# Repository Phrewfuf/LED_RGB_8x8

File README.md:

LED_RGB_8x8
===========

Proof of concept for a bigger RGB LED Project

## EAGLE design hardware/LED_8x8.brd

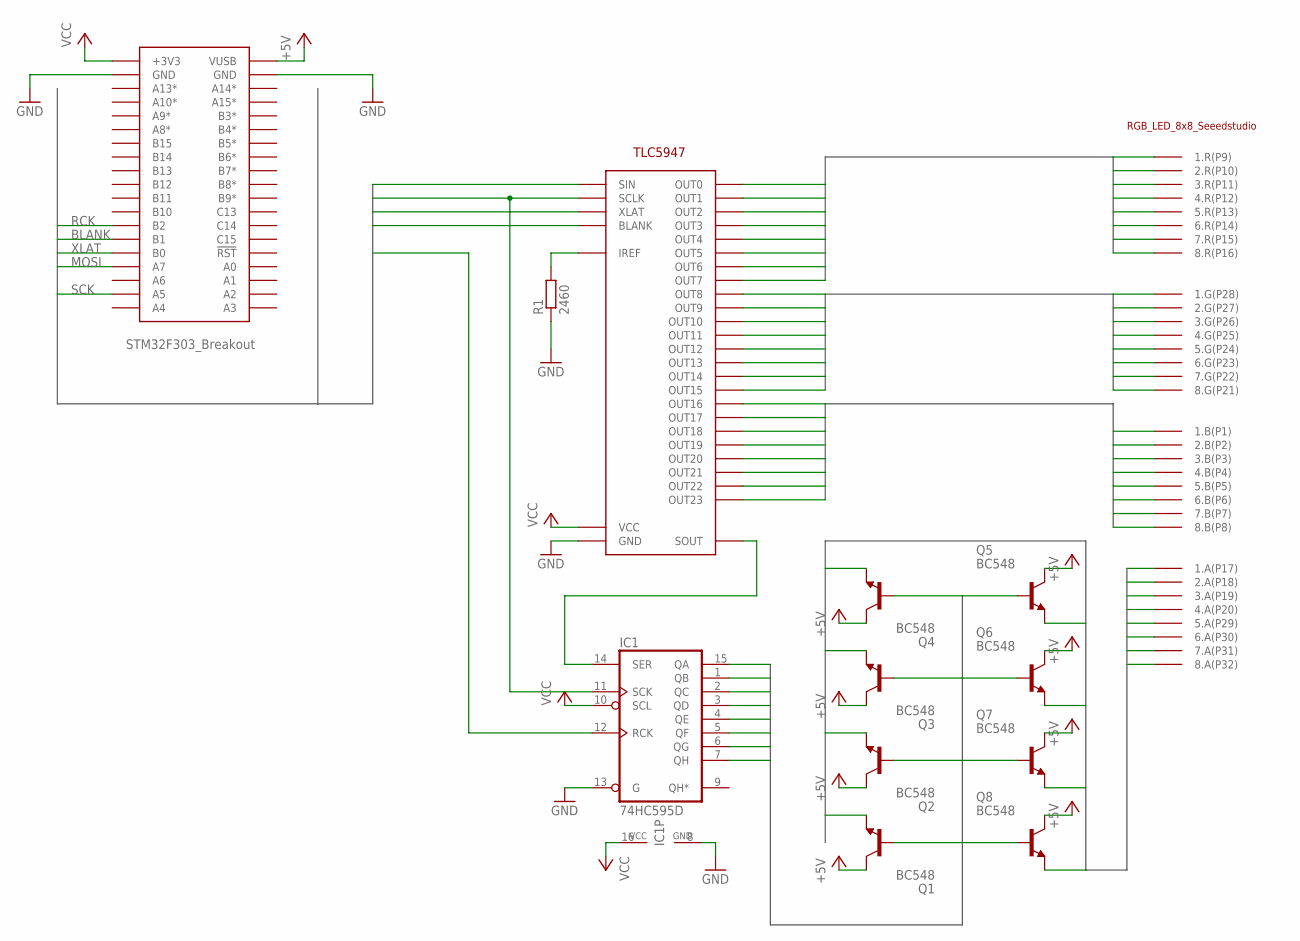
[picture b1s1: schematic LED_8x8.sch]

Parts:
IC1: 74HC595D; SO16
Q1, Q2, Q3, Q4, Q5, Q6, Q7, Q8: BC548; TO92-EBC
R1: 2460; R0603
U$1: TLC5947; TSSOP32
U$2: STM32F303_BREAKOUT; STM32_BREAKOUT
U$3: LED_RGB_8X8

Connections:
+5V: Q1.C, Q2.C, Q3.C, Q4.C, Q5.C, Q6.C, Q7.C, Q8.C, U$2.VUSB
BLANK: U$1.BLANK, U$2.B1
BLUE1: U$1.OUT16, U$3.P1 (1.B(P1))
BLUE2: U$1.OUT17, U$3.P2 (2.B(P2))
BLUE3: U$1.OUT18, U$3.P3 (3.B(P3))
BLUE4: U$1.OUT19, U$3.P4 (4.B(P4))
BLUE5: U$1.OUT20, U$3.P5 (5.B(P5))
BLUE6: U$1.OUT21, U$3.P6 (6.B(P6))
BLUE7: U$1.OUT22, U$3.P7 (7.B(P7))
BLUE8: U$1.OUT23, U$3.P8 (8.B(P8))
GND: IC1.8 (GND), IC1.13 (G), R1.1, U$1.GND, U$2.GND@1 (GND), U$2.GND@2 (GND)
GREEN1: U$1.OUT8, U$3.P28 (1.G(P28))
GREEN2: U$1.OUT9, U$3.P27 (2.G(P27))
GREEN3: U$1.OUT10, U$3.P26 (3.G(P26))
GREEN4: U$1.OUT11, U$3.P25 (4.G(P25))
GREEN5: U$1.OUT12, U$3.P24 (5.G(P24))
GREEN6: U$1.OUT13, U$3.P23 (6.G(P23))
GREEN7: U$1.OUT14, U$3.P22 (7.G(P22))
GREEN8: U$1.OUT15, U$3.P21 (8.G(P21))
MOSI: U$1.SIN, U$2.A7
unnamed: IC1.14 (SER), U$1.SOUT
unnamed: R1.2, U$1.IREF
POWERA1: Q1.E, U$3.P17 (1.A(P17))
POWERA2: Q2.E, U$3.P18 (2.A(P18))
POWERA3: Q3.E, U$3.P19 (3.A(P19))
POWERA4: Q4.E, U$3.P20 (4.A(P20))
POWERA5: Q5.E, U$3.P29 (5.A(P29))
POWERA6: Q6.E, U$3.P30 (6.A(P30))
POWERA7: Q7.E, U$3.P31 (7.A(P31))
POWERA8: Q8.E, U$3.P32 (8.A(P32))
RCK: IC1.12 (RCK), U$2.B2
RED1: U$1.OUT0, U$3.P9 (1.R(P9))
RED2: U$1.OUT1, U$3.P10 (2.R(P10))
RED3: U$1.OUT2, U$3.P11 (3.R(P11))
RED4: U$1.OUT3, U$3.P12 (4.R(P12))
RED5: U$1.OUT4, U$3.P13 (5.R(P13))
RED6: U$1.OUT5, U$3.P14 (6.R(P14))
RED7: U$1.OUT6, U$3.P15 (7.R(P15))
RED8: U$1.OUT7, U$3.P16 (8.R(P16))
SCK: IC1.11 (SCK), U$1.SCLK, U$2.A5
SHIFTA1: IC1.15 (QA), Q1.B
SHIFTA2: IC1.1 (QB), Q2.B
SHIFTA3: IC1.2 (QC), Q3.B
SHIFTA4: IC1.3 (QD), Q4.B
SHIFTA5: IC1.4 (QE), Q5.B
SHIFTA6: IC1.5 (QF), Q6.B
SHIFTA7: IC1.6 (QG), Q7.B
SHIFTA8: IC1.7 (QH), Q8.B
VCC: IC1.10 (SCL), IC1.16 (VCC), U$1.VCC, U$2.+3V3
XLAT: U$1.XLAT, U$2.B0

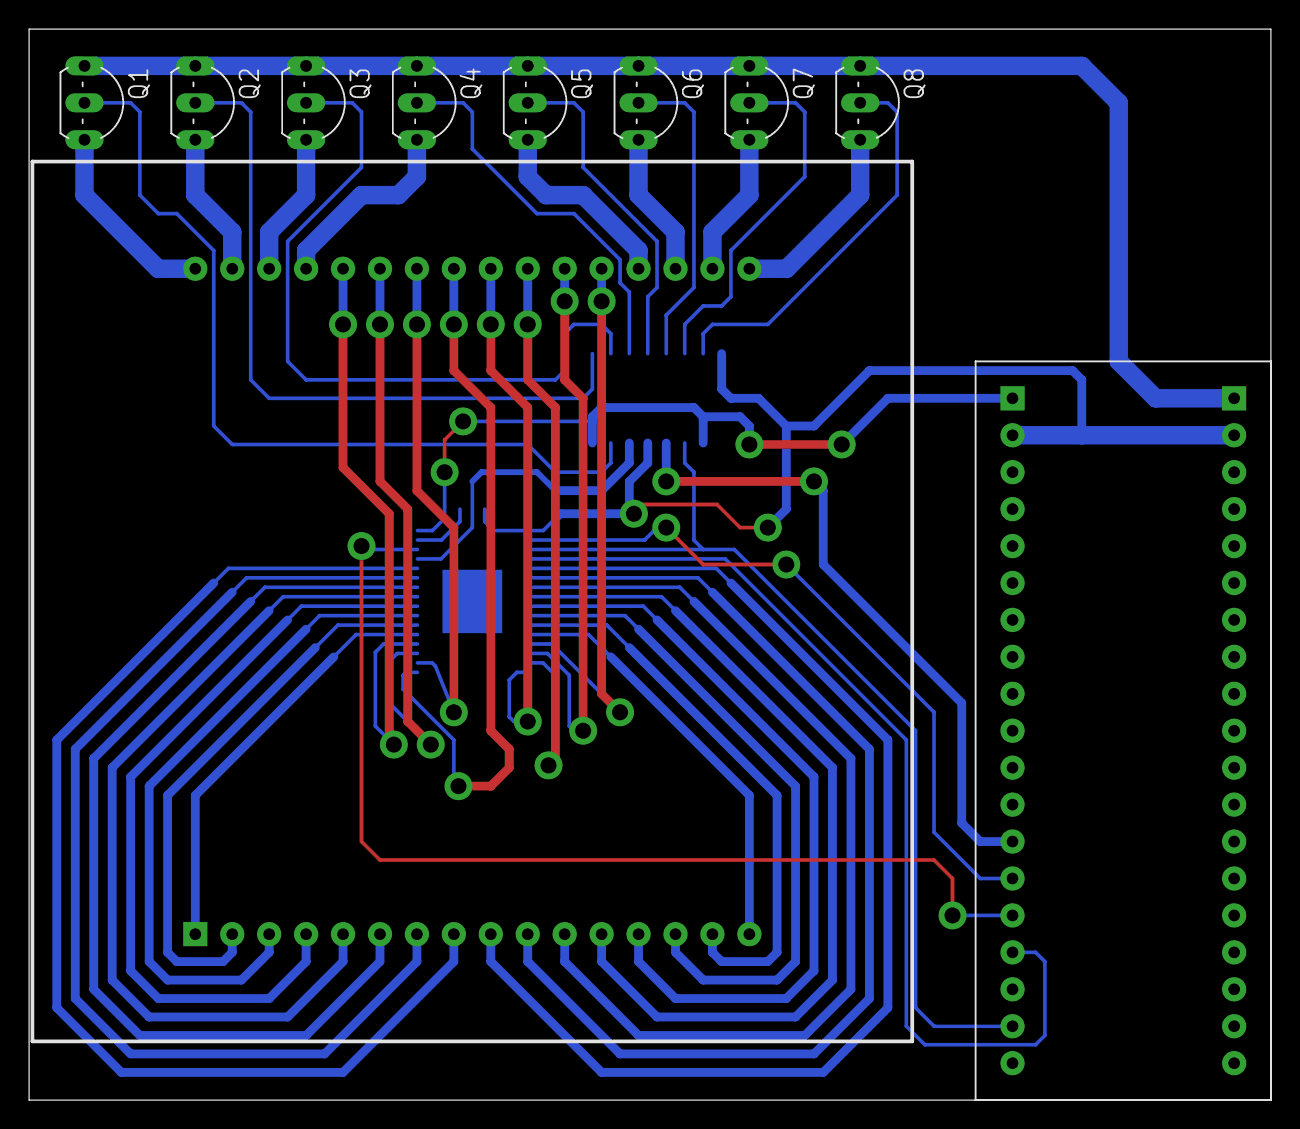
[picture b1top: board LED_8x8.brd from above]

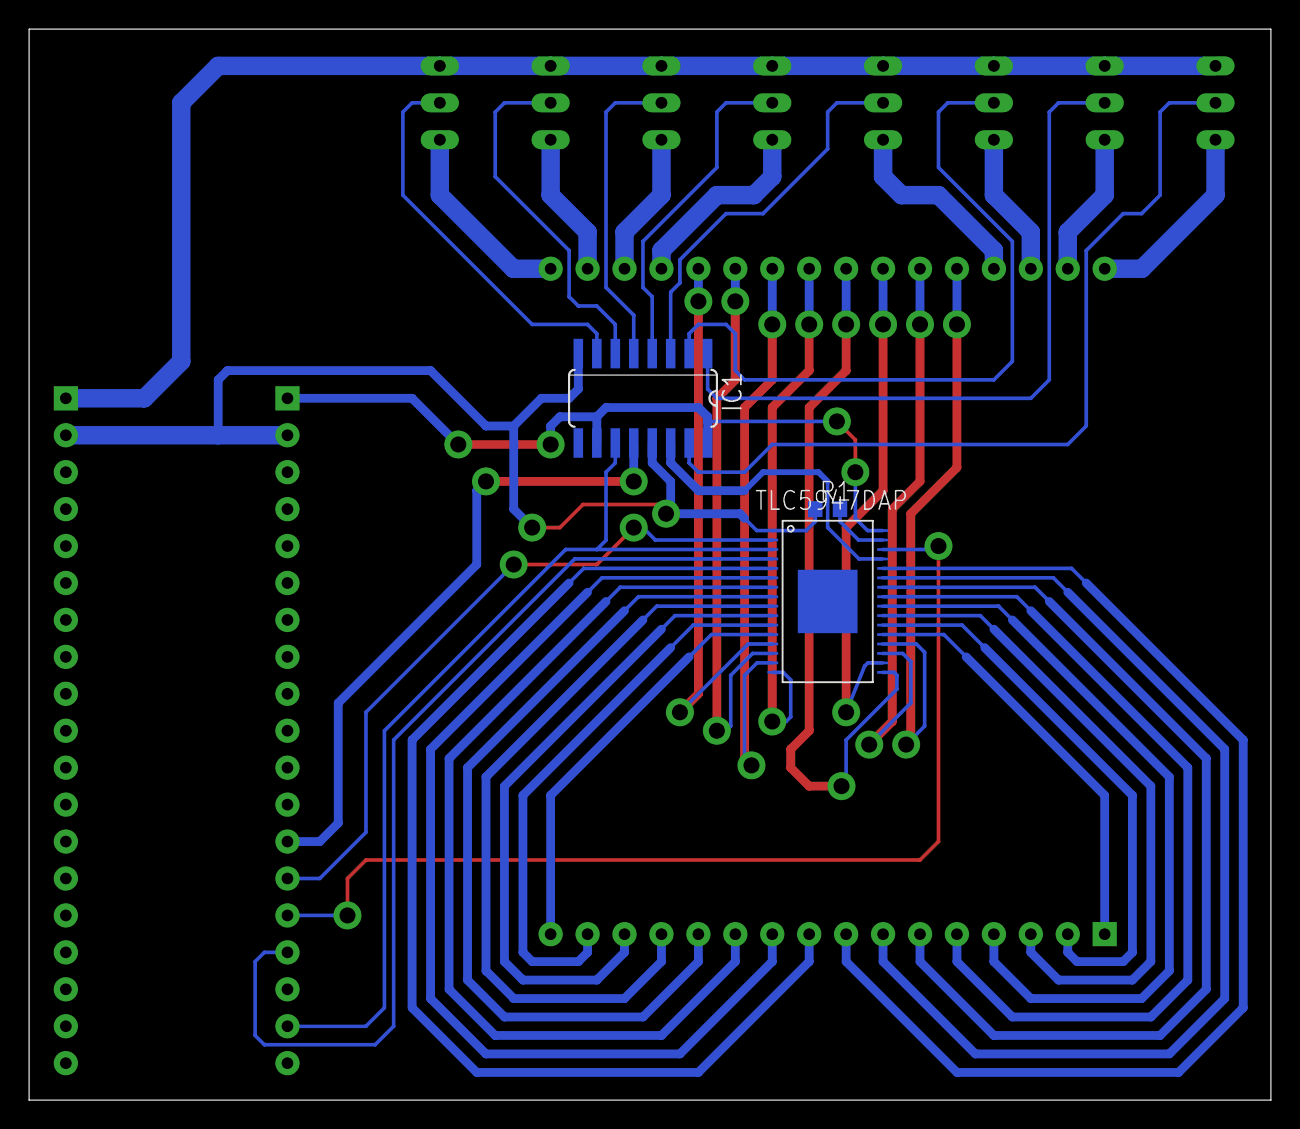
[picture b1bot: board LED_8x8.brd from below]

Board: 2 copper layers, 85.4 x 73.7 mm, 13 parts (3 on the bottom side), 50 nets.

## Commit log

2013-04-10 created and added first parts to schematic
2013-04-10 edited readme
2013-04-11 progress, bitches
2013-04-12 added schematic
2013-04-13 schematic sucked
2013-04-14 finished layout
2013-04-14 resized drills and vias
2013-04-14 minor corrections
